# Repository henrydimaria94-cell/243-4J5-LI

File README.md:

# Labo 04 — Communication LoRa avec LilyGo T-Beam Supreme

Communication bidirectionnelle LoRa entre deux modules LilyGo T-Beam Supreme S3.  
Le transmetteur envoie la valeur d'un potentiomètre ; le récepteur interroge un LLM via l'API Groq, renvoie la réponse par LoRa et publie les métriques sur un broker MQTT.

## Architecture du système

```
[Transmetteur]                              [Récepteur]
  Potentiomètre                               SX1262 (LoRa)
       │                                           │
  SX1262 (LoRa) ──── 915 MHz / SF9 ──────►  WiFi → API Groq (LLM)
       │                                           │
  OLED SH1106   ◄──── réponse texte ────────  MQTT WebSocket TLS
  LED GPIO 43                                 LED GPIO 43
```

## Matériel requis

| Composant | Quantité |
|-----------|----------|
| LilyGo T-Beam Supreme S3 (SX1262) | 2 |
| Potentiomètre (branché sur GPIO 2) | 1 |

## Structure du projet

```
Labo-04-TP/
├── transmitter/
│   ├── transmitter.ino       # Sketch émetteur LoRa
│   ├── LoRaBoards.h/.cpp     # Abstraction matérielle LilyGo
│   └── utilities.h           # Définitions des broches
│
├── receiver/
│   ├── receiver.ino          # Sketch récepteur LoRa + LLM + MQTT
│   ├── config.example.h      # ← Modèle de configuration
│   ├── config.h              # ← À créer (ignoré par Git)
│   ├── LoRaBoards.h/.cpp
│   └── utilities.h
│
└── llm-t-beam-supreme/       # Sketch autonome test LLM sans LoRa
```

## Installation

### 1. Cloner le dépôt

```bash
git clone <url-du-repo>
```

### 2. Créer le fichier de configuration

```bash
cp receiver/config.example.h receiver/config.h
```

Ouvrez `receiver/config.h` et remplissez vos valeurs :

```cpp
// WiFi personnel
#define WIFI_SECURITY_WPA2_PERSONAL
const char* WIFI_SSID     = "MonReseau";
const char* WIFI_PASSWORD = "MonMotDePasse";

// API Groq — https://console.groq.com
const char* API_KEY = "gsk_...";

// MQTT
const char* MQTT_BROKER = "votre-broker.exemple.com";
const char* MQTT_USER   = "utilisateur";
const char* MQTT_PASS   = "motdepasse";

// Topics — adaptez le préfixe
const char* MQTT_TOPIC_POT     = "prenom-nom/pot";
const char* MQTT_TOPIC_REPONSE = "prenom-nom/reponse";
const char* MQTT_TOPIC_RSSI    = "prenom-nom/rssi";
const char* MQTT_TOPIC_SNR     = "prenom-nom/snr";
```

> `config.h` est listé dans `.gitignore` — il ne sera jamais commité.

### 3. Librairies Arduino requises

Installez via le gestionnaire de librairies Arduino IDE :

| Librairie | Auteur |
|-----------|--------|
| ArduinoJson | Benoit Blanchon |
| U8g2 | olikraus |
| XPowersLib | Lewis He |
| RadioLib | jgromes |
| PubSubClient | Nick O'Leary |

### 4. Sélectionner la carte

**Tools → Board → ESP32S3 Dev Module**

| Paramètre | Valeur |
|-----------|--------|
| USB CDC On Boot | Enabled |
| Flash Size | 16MB |
| PSRAM | OPI PSRAM |

### 5. Téléverser

1. Téléverser `transmitter/transmitter.ino` sur le premier T-Beam.
2. Téléverser `receiver/receiver.ino` sur le second T-Beam.

## Paramètres LoRa

| Paramètre | Valeur |
|-----------|--------|
| Fréquence | 915.0 MHz |
| Bande passante | 125 kHz |
| Spreading Factor | 9 |
| Coding Rate | 7 |
| Sync Word | 0x12 |
| Puissance TX | 14 dBm |
| Préambule | 16 |
| CRC | Activé |

## Format des messages LoRa

**Transmetteur → Récepteur**
```json
{ "pot": 2048 }
```

**Récepteur → Transmetteur**
```
Texte brut — réponse du LLM (max 40 caractères)
```

## Topics MQTT publiés par le récepteur

| Topic | Contenu |
|-------|---------|
| `{prefix}/pot` | Valeur du potentiomètre (0–4095) |
| `{prefix}/reponse` | Réponse du LLM |
| `{prefix}/rssi` | RSSI LoRa (dBm) |
| `{prefix}/snr` | SNR LoRa (dB) |

## Comportement du transmetteur

- Lecture continue du potentiomètre (GPIO 2, ADC 12 bits, 0–4095)
- Envoi si valeur stable ≥ 400 ms **et** variation > 80 unités depuis le dernier envoi
- Délai minimal de 3 secondes entre deux transmissions
- Attente de la réponse du récepteur (timeout 30 s)
- LED GPIO 43 : 3 flashs rapides à l'envoi, puis fixe selon l'effort (HIGH si pot > 2048)

## Comportement du récepteur

- Réception LoRa par interruption (DIO1)
- Appel API Groq dès réception d'un paquet valide
- Retransmission de la réponse texte au transmetteur
- Publication MQTT sur 4 topics
- Affichage OLED avec retour écran veille après 10 secondes
- LED GPIO 43 : allumée pendant le traitement LLM

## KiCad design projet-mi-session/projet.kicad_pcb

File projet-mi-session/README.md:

# Projet Mi-Session — Jeu de Labyrinthe IoT
**Cours :** 243-4J5-LI
**Étudiant :** Henri-Tadja

---

## Description
Un labyrinthe généré procéduralement s'affiche sur l'écran tactile du Raspberry Pi 5.
Le joueur incline le shield LilyGO A7670G pour déplacer une balle dorée jusqu'à la sortie via le MPU6050 (roll/pitch).

---

## Architecture
```
Shield LilyGO A7670G                   Raspberry Pi 5 (écran tactile)
─────────────────────                  ─────────────────────────────
Incliner le shield    ──── LTE/MQTT ──→  Balle se déplace dans le labyrinthe
BTN1 : Démarrer/Reprendre              Labyrinthe + capteurs temps réel
BTN2 : Pause/Reprendre                 Boutons tactiles : Start/Pause/Reset
BTN3 : Reset                           Chronomètre + meilleur temps
POT1 : Difficulté (1–3)
POT2 : Vitesse balle (1–5)
POT3 : Taille labyrinthe (S/M/L)
LED1 : Allumée pendant la partie, clignote à la victoire
```

---

## Broches GPIO

| Composant   | Broche  | Rôle                         |
|-------------|---------|------------------------------|
| BTN1        | GPIO 13 | Démarrer / Reprendre         |
| BTN2        | GPIO 14 | Pause / Reprendre            |
| BTN3        | GPIO 27 | Reset                        |
| LED rouge   | GPIO 25 | Feedback (partie / victoire) |
| POT1        | GPIO 32 | Difficulté (1–3)             |
| POT2        | GPIO 33 | Vitesse (1–5)                |
| POT3        | GPIO 34 | Taille du labyrinthe (S/M/L) |
| MPU6050 SDA | GPIO 21 | I2C données                  |
| MPU6050 SCL | GPIO 22 | I2C horloge                  |

---

## Structure du projet
```
projet-mi-session/
├── firmware/
│   ├── firmware.ino          # Code principal LilyGO A7670G
│   ├── auth.h.example        # Template credentials MQTT
│   ├── auth.h                # Credentials réels (ne pas committer !)
│   ├── trust_anchors.h       # Certificats TLS
│   └── tests/
│       └── checklist.md      # Checklist validation firmware
├── interface/
│   ├── main.py               # Interface pygame + MQTT (Raspberry Pi)
│   ├── requirements.txt      # Dépendances Python
│   ├── iot-interface.service # Service systemd
│   └── tests/
│       └── checklist.md      # Checklist validation interface
└── README.md
```

---

## Topics MQTT

| Direction     | Topic                                        |
|---------------|----------------------------------------------|
| LilyGO → Pi  | `etudiant/henri-tadja/sensors/buttons`       |
| LilyGO → Pi  | `etudiant/henri-tadja/sensors/pots`          |
| LilyGO → Pi  | `etudiant/henri-tadja/sensors/accel`         |
| LilyGO → Pi  | `etudiant/henri-tadja/game/state`            |
| LilyGO → Pi  | `etudiant/henri-tadja/status`                |
| Pi → LilyGO  | `etudiant/henri-tadja/actuators/led1`        |
| Pi → LilyGO  | `etudiant/henri-tadja/game/command`          |

---

## Installation firmware (LilyGO)
```bash
cd ~/243-4J5-LI/projet-mi-session/firmware
cp auth.h.example auth.h
nano auth.h
arduino-cli compile --fqbn esp32:esp32:esp32 firmware.ino
arduino-cli upload -p /dev/ttyUSB0 --fqbn esp32:esp32:esp32 firmware.ino
arduino-cli monitor -p /dev/ttyUSB0 -c baudrate=115200
```

---

## Installation interface (Raspberry Pi)
```bash
cd ~/243-4J5-LI/projet-mi-session/interface
pip3 install -r requirements.txt --break-system-packages
python3 main.py
```

---

## Démarrage automatique (systemd)
```bash
sudo cp iot-interface.service /etc/systemd/system/
sudo systemctl daemon-reload
sudo systemctl enable iot-interface.service
sudo systemctl start iot-interface.service
sudo systemctl status iot-interface.service
```

---

## Git — Remise finale
```bash
cd ~/243-4J5-LI/projet-mi-session
git add .
git commit -m "Projet mi-session : système IoT complet"
git push origin henri-tadja/projet-mi-session
```

> ⚠️ Ne jamais committer `auth.h` — vérifier que `.gitignore` contient `auth.h`

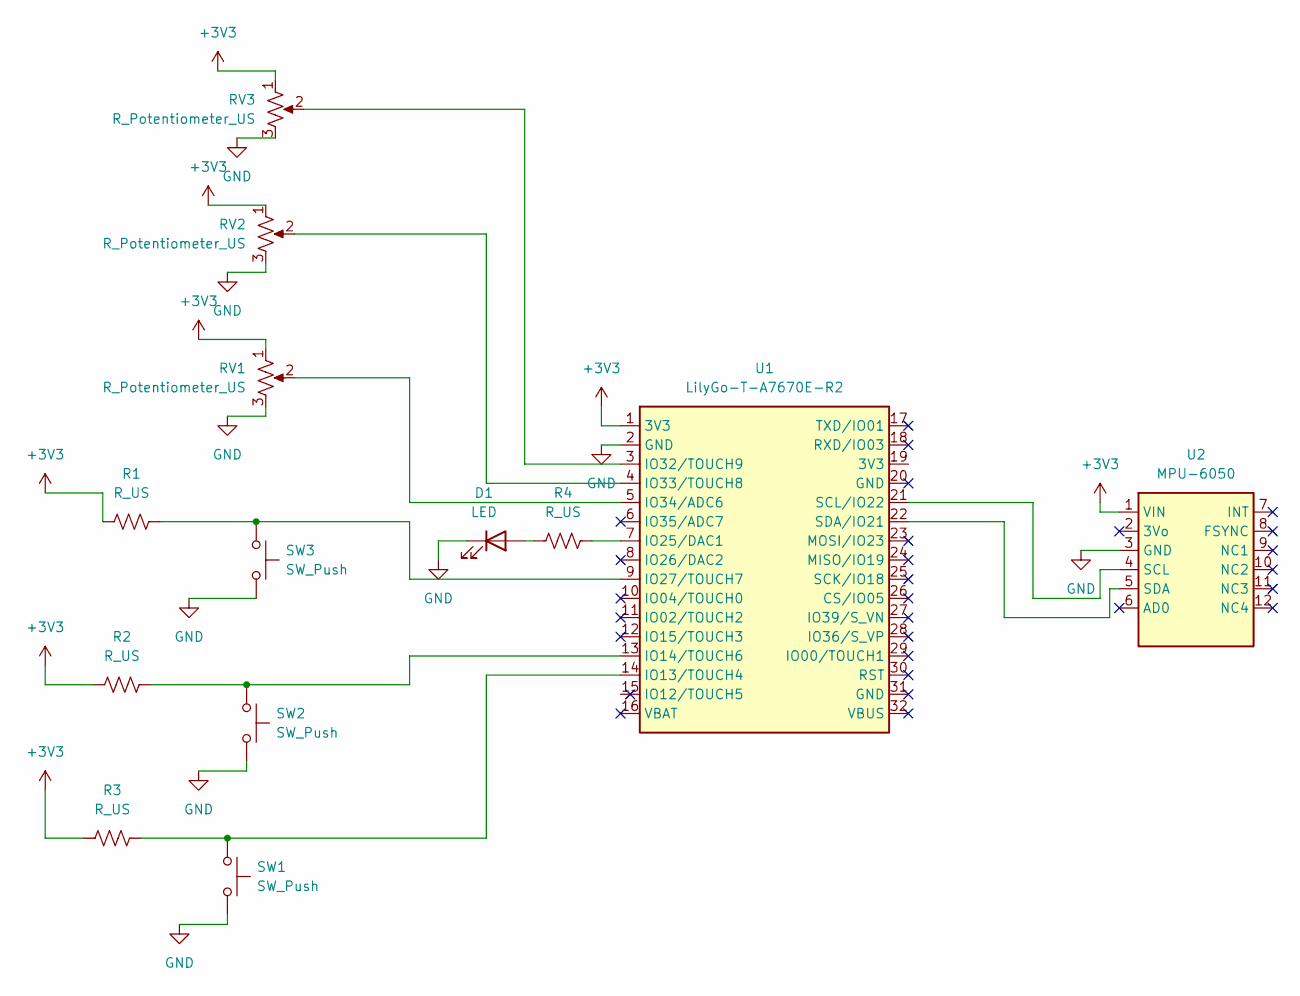
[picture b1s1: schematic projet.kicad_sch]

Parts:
D1: LED; LED_D5.0mm
R1, R2, R3, R4: R_US; R_Axial_DIN0207_L6.3mm_D2.5mm_P7.62mm_Horizontal
RV1, RV2, RV3: R_Potentiometer_US; Potentiometer_Bourns_3386P_Vertical
SW1, SW2, SW3: SW_Push; SW_B3WN-600x_OMR
U1: LilyGo-T-A7670E-R2; LilyGO_T-A7670E-R2
U2: MPU-6050; MPU-6050_Breakout

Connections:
+3V3: R1.1, R2.1, R3.1, RV1.1, RV2.1, RV3.1, U1.1 (3V3), U2.1 (VIN)
GND: D1.1 (K), RV1.3, RV2.3, RV3.3, SW1.2, SW2.2, SW3.2, U1.2 (GND), U2.3 (GND)
unnamed: D1.2 (A), R4.1
unnamed: R3.2, SW1.1, U1.14 (IO13/TOUCH4)
unnamed: R2.2, SW2.1, U1.13 (IO14/TOUCH6)
unnamed: R4.2, U1.7 (IO25/DAC1)
unnamed: R1.2, SW3.1, U1.9 (IO27/TOUCH7)
unnamed: RV3.2, U1.3 (IO32/TOUCH9)
unnamed: RV2.2, U1.4 (IO33/TOUCH8)
unnamed: RV1.2, U1.5 (IO34/ADC6)
unnamed: U1.21 (SCL/IO22), U2.4 (SCL)
unnamed: U1.22 (SDA/IO21), U2.5 (SDA)

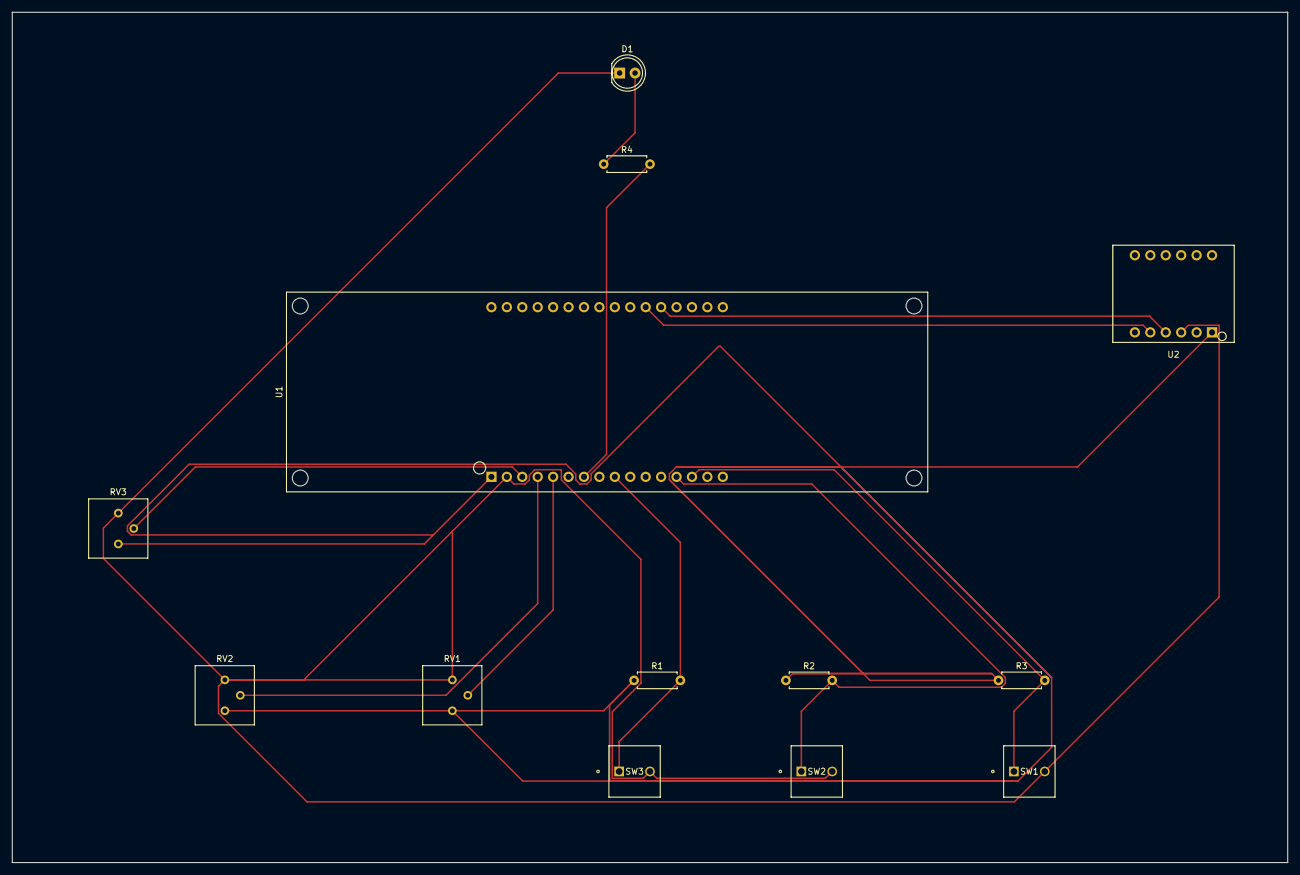
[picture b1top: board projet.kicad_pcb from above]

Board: 2 copper layers, 210.0 x 140.0 mm, 13 parts (0 on the bottom side), 12 nets.

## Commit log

2026-02-12 Ajout du contrôle de LEDs via interface tactile et port série
2026-02-12 Préparation Labo 2: installation Mosquitto et test WiFi ESP32
2026-02-21 Ajout Labo-02 : lilygo_lte_mqtt_toggle - Henri Tadja
2026-03-23 Projet mi-session : système IoT complet
2026-03-26 Projet-mi-session:systeme IOT complet
2026-03-26 Kicad
2026-03-30 fabriction gerber
2026-03-30 docs
